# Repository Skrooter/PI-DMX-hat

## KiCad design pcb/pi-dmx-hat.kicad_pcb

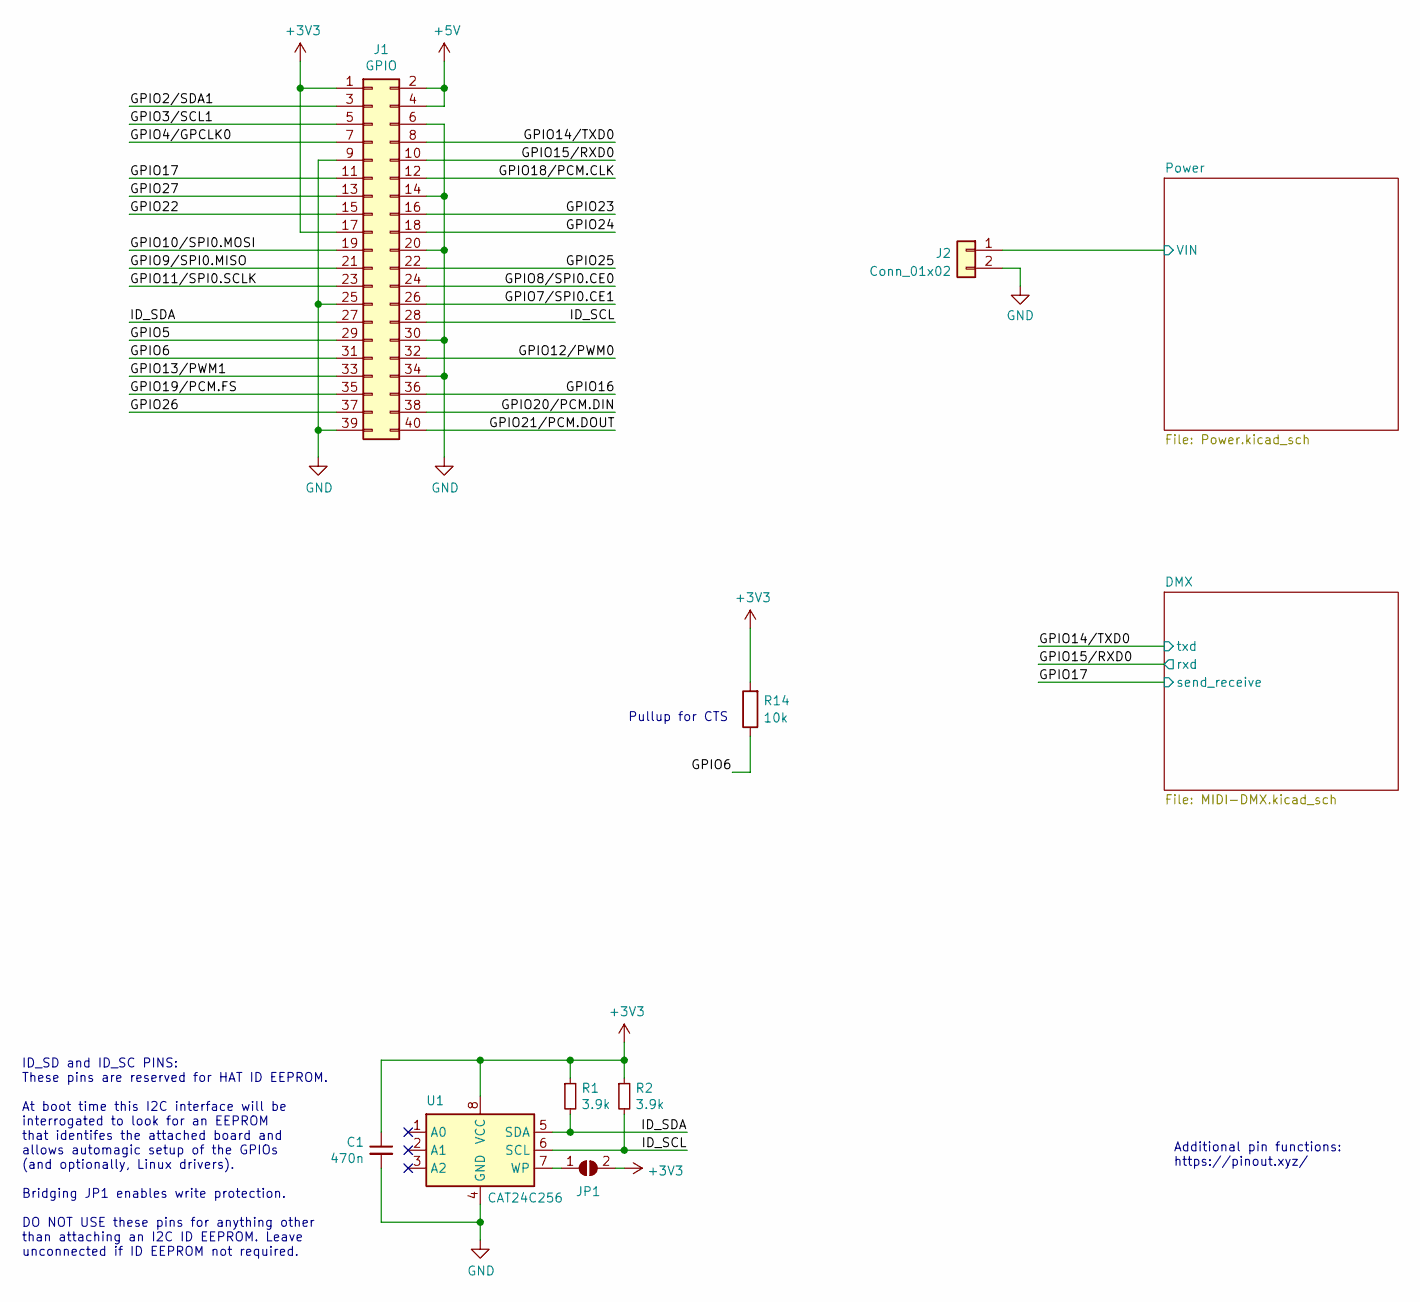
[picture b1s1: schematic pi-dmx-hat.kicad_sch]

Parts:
C1: 470n; C_0402_1005Metric; LCSC C307331
J1: GPIO; PinSocket_2x20_P2.54mm_Vertical
J2: Conn_01x02; PhoenixContact_MC_1,5_2-G-3.81_1x02_P3.81mm_Horizontal
JP1: ID_WP; SolderJumper-2_P1.3mm_Open_TrianglePad1.0x1.5mm
R1, R2: 3.9k; R_0603_1608Metric; LCSC C23018
R14: 10k; R_0402_1005Metric; LCSC C25744
U1: CAT24C256; DFN-8-1EP_3x2mm_P0.5mm_EP1.3x1.5mm; LCSC C233771

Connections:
+3V3: C1.1, J1.1, J1.17, JP1.2 (B), R1.1, R2.1, R14.2, U1.8 (VCC); also elsewhere on the board
+5V: J1.2, J1.4; also elsewhere on the board
/GPIO2/SDA1: J1.3
/GPIO3/SCL1: J1.5
/GPIO4/GPCLK0: J1.7
/GPIO5: J1.29
/GPIO6: J1.31, R14.1
/GPIO7/SPI0.CE1: J1.26
/GPIO8/SPI0.CE0: J1.24
/GPIO9/SPI0.MISO: J1.21
/GPIO10/SPI0.MOSI: J1.19
/GPIO11/SPI0.SCLK: J1.23
/GPIO12/PWM0: J1.32
/GPIO13/PWM1: J1.33
/GPIO14/TXD0: J1.8; also elsewhere on the board
/GPIO15/RXD0: J1.10; also elsewhere on the board
/GPIO16: J1.36
/GPIO17: J1.11; also elsewhere on the board
/GPIO18/PCM.CLK: J1.12
/GPIO19/PCM.FS: J1.35
/GPIO20/PCM.DIN: J1.38
/GPIO21/PCM.DOUT: J1.40
/GPIO22: J1.15
/GPIO23: J1.16
/GPIO24: J1.18
/GPIO25: J1.22
/GPIO26: J1.37
/GPIO27: J1.13
/ID_SCL: J1.28, R2.2, U1.6 (SCL)
/ID_SDA: J1.27, R1.2, U1.5 (SDA)
/Power/VIN: J2.1; also elsewhere on the board
GND: C1.2, J1.6, J1.9, J1.14, J1.20, J1.25, J1.30, J1.34, J1.39, J2.2, U1.4 (GND); also elsewhere on the board
unnamed: JP1.1 (A), U1.7 (WP)

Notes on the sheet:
Additional pin functions: https://pinout.xyz/
ID_SD and ID_SC PINS: These pins are reserved for HAT ID EEPROM. At boot time this I2C interface will be interrogated to look for an EEPROM that identifes the attached board and allows automagic setup of the GPIOs (and optionally, Linux drivers). Bridging JP1 enables write protection. DO NOT USE th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
Pullup for CTS

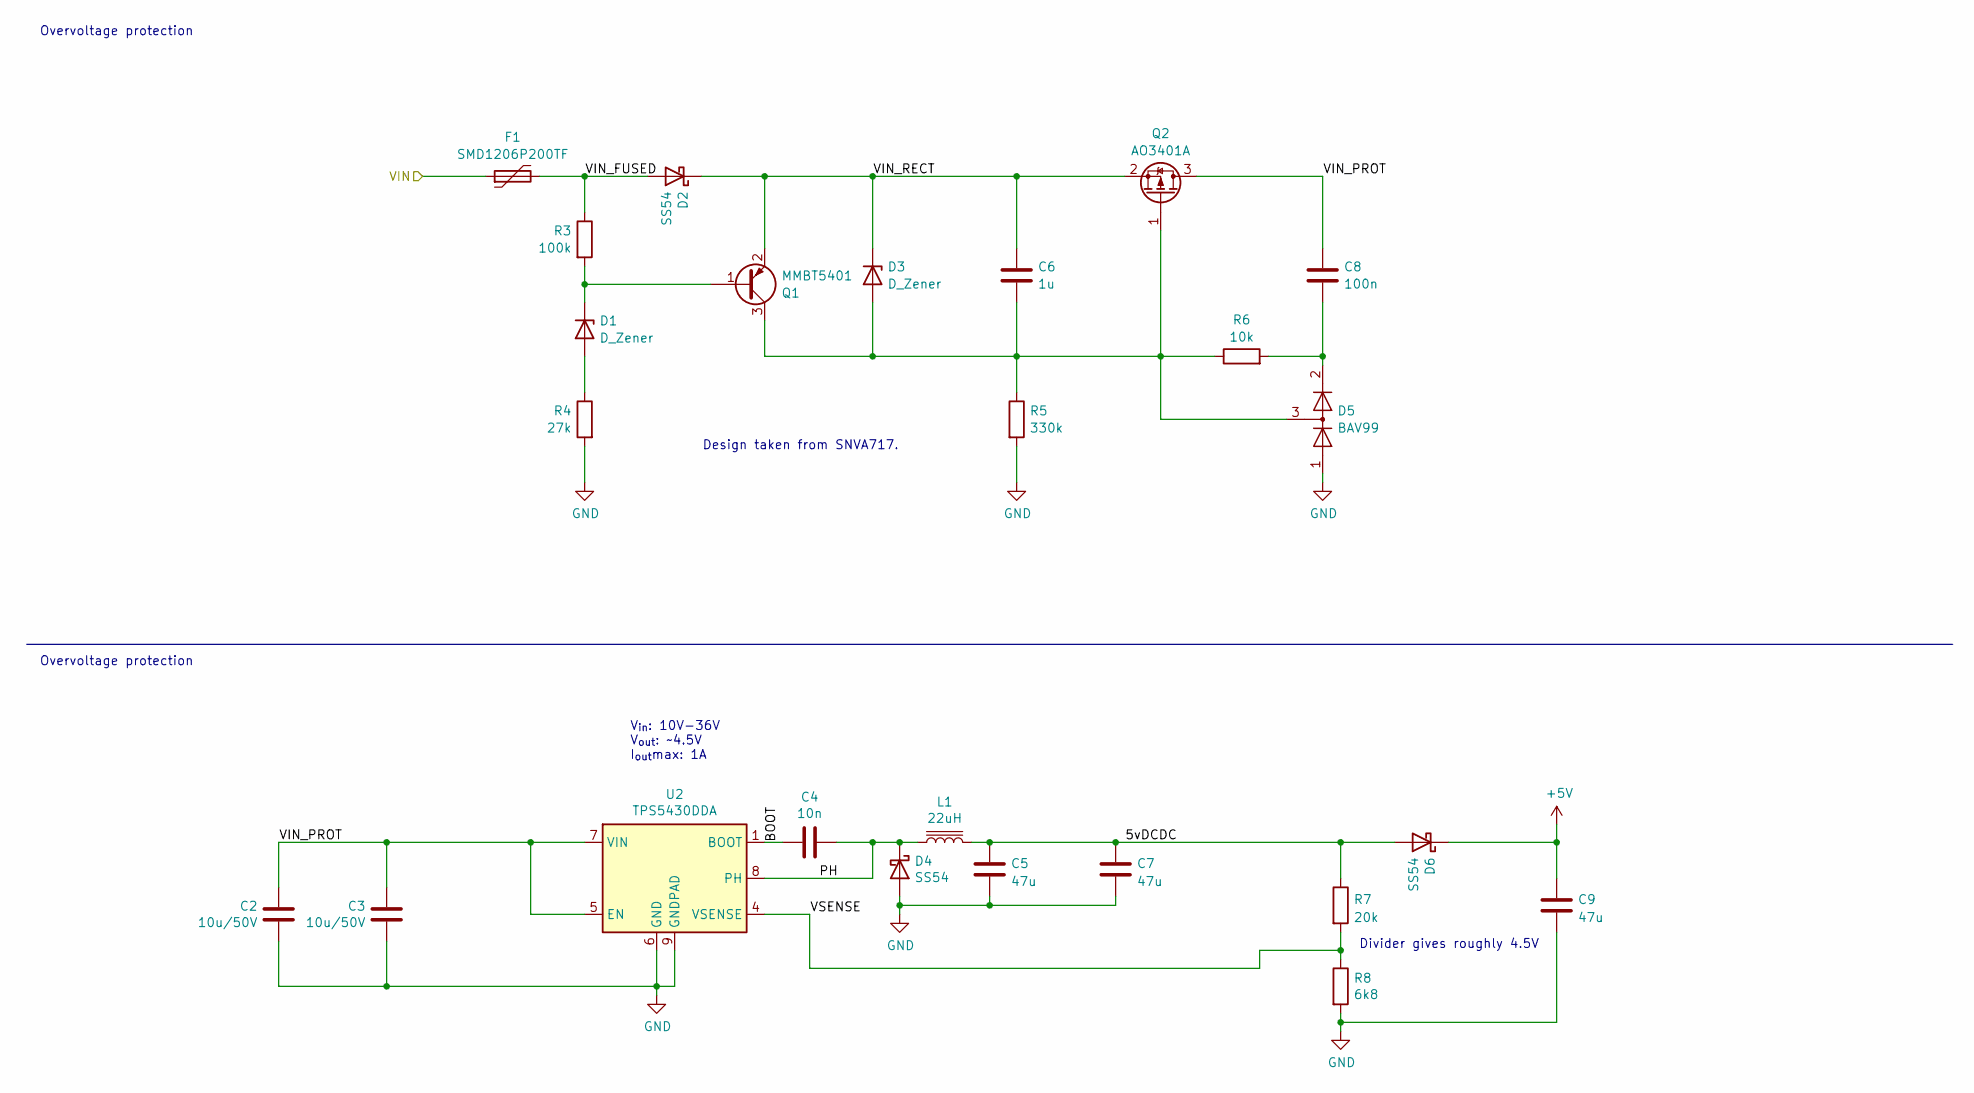
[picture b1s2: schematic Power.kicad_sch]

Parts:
C2, C3: 10u/50V; C_1206_3216Metric_Pad1.33x1.80mm_HandSolder; LCSC C13585
C4: 10n; C_0603_1608Metric_Pad1.08x0.95mm_HandSolder; LCSC C57112
C5, C7, C9: 47u; C_0805_2012Metric; LCSC C1779
C6: 1u; C_0805_2012Metric; LCSC C28323
C8: 100n; C_0402_1005Metric; LCSC C307331
D1, D3: D_Zener; D_SOD-123; LCSC C209348
D2, D4, D6: SS54; D_SMA; LCSC C22452
D5: BAV99; SOT-23; LCSC C2500
F1: SMD1206P200TF; Fuse_1206_3216Metric; LCSC C20988
L1: 22uH; L_Vishay_IHLP-4040; LCSC C845072
Q1: MMBT5401; SOT-23; LCSC C8326
Q2: AO3401A; SOT-23; LCSC C15127
R3: 100k; R_0402_1005Metric; LCSC C25741
R4: 27k; R_0603_1608Metric; LCSC C22967
R5: 330k; R_0603_1608Metric; LCSC C23137
R6: 10k; R_0402_1005Metric; LCSC C25744
R7: 20k; R_0603_1608Metric_Pad0.98x0.95mm_HandSolder; LCSC C4184
R8: 6k8; R_0603_1608Metric_Pad0.98x0.95mm_HandSolder; LCSC C23212
U2: TPS5430DDA; TI_SO-PowerPAD-8_ThermalVias; LCSC C9864

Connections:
+5V: C9.1, D6.1 (K); also elsewhere on the board
/Power/5vDCDC: C5.1, C7.1, D6.2 (A), L1.2, R7.1
/Power/BOOT: C4.2, U2.1 (BOOT)
/Power/PH: C4.1, D4.1 (K), L1.1, U2.8 (PH)
/Power/VIN: F1.1; also elsewhere on the board
/Power/VIN_FUSED: D2.2 (A), F1.2, R3.1
/Power/VIN_PROT: C2.2, C3.2, C8.1, Q2.3 (D), U2.5 (EN), U2.7 (VIN)
/Power/VIN_RECT: C6.1, D2.1 (K), D3.1 (K), Q1.2 (E), Q2.2 (S)
/Power/VSENSE: R7.2, R8.1, U2.4 (VSENSE)
GND: C2.1, C3.1, C5.2, C7.2, C9.2, D4.2 (A), D5.1 (K), R4.2, R5.2, R8.2, U2.6 (GND), U2.9 (GNDPAD); also elsewhere on the board
unnamed: D1.2 (A), R4.1
unnamed: D1.1 (K), Q1.1 (B), R3.2
unnamed: C6.2, D3.2 (A), D5.3 (K), Q1.3 (C), Q2.1 (G), R5.1, R6.1
unnamed: C8.2, D5.2 (A), R6.2

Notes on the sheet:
Divider gives roughly 4.5V
Overvoltage protection
V_{in}: 10V-36V V_{out}: ~4.5V I_{out}max: 1A
Design taken from SNVA717.

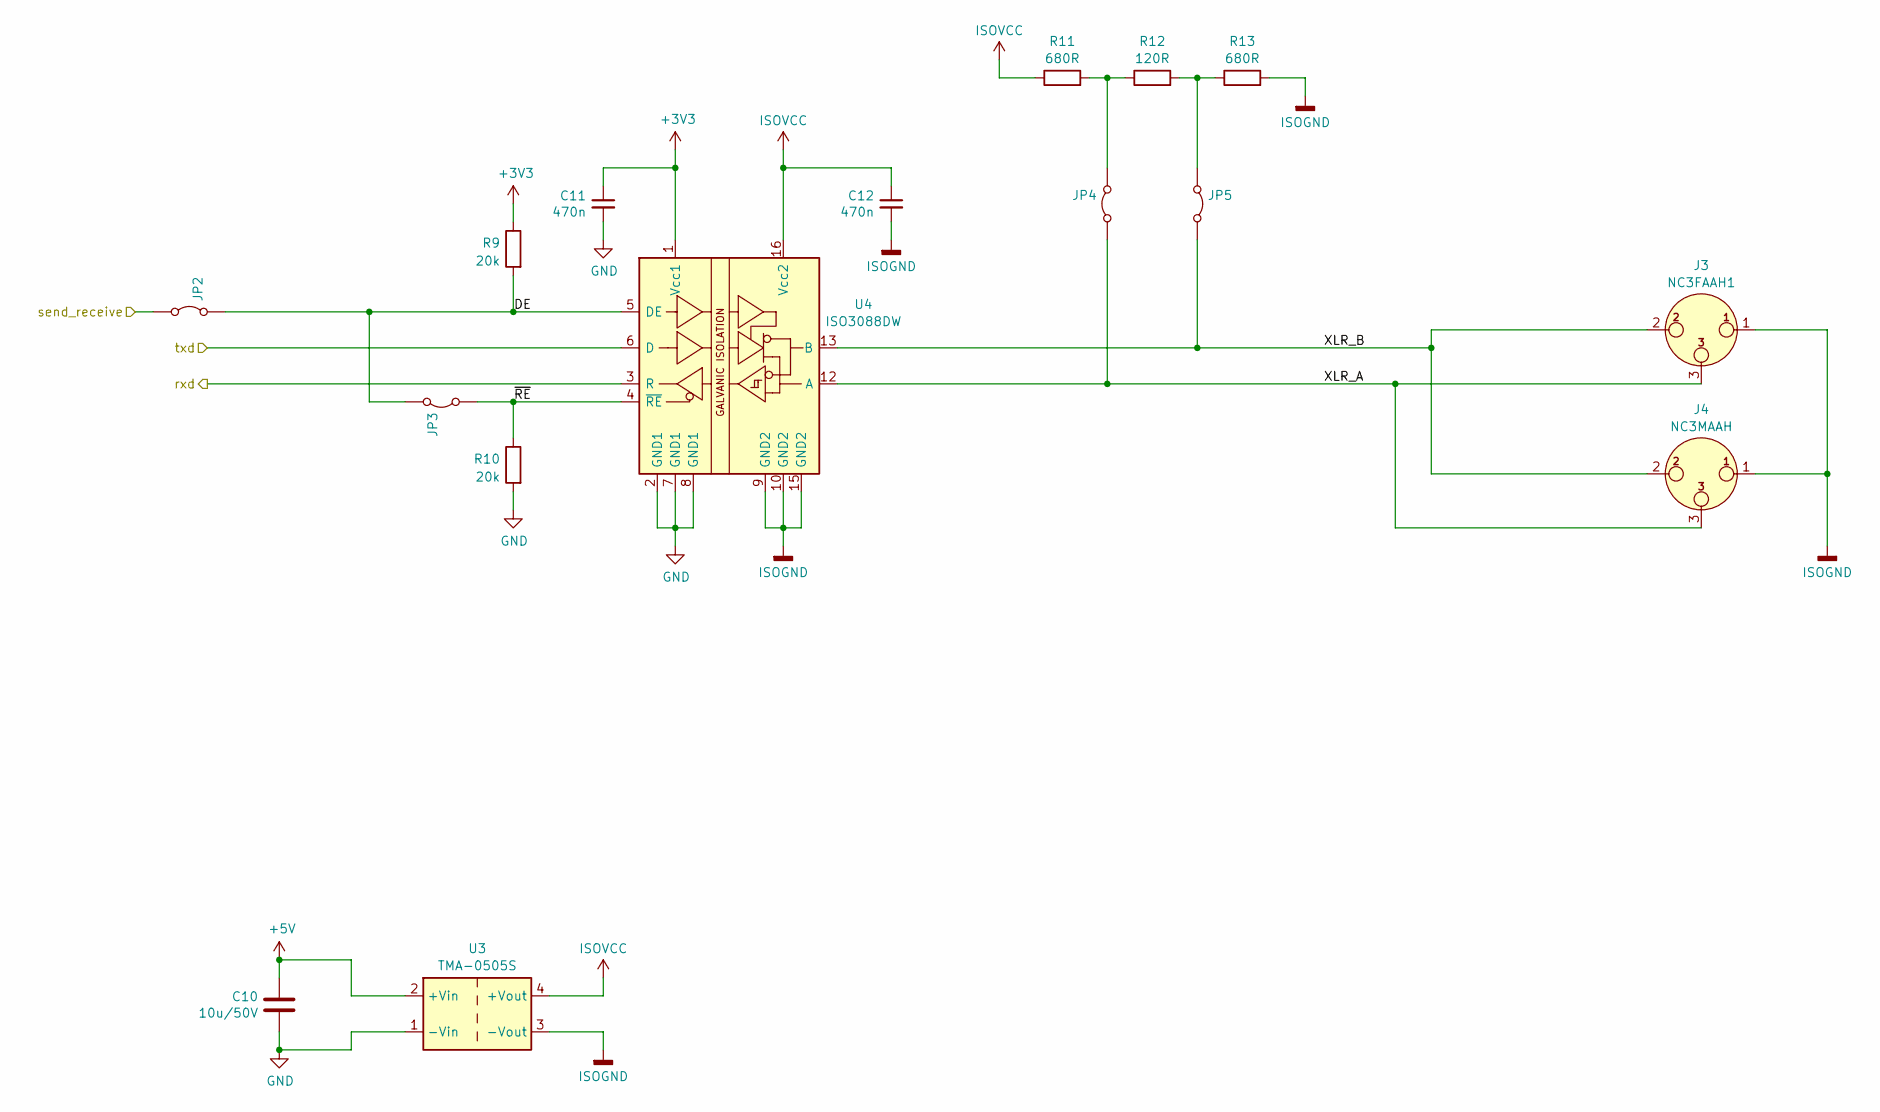
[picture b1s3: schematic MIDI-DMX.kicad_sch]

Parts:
C10: 10u/50V; C_1206_3216Metric_Pad1.33x1.80mm_HandSolder; LCSC C13585
C11, C12: 470n; C_0402_1005Metric; LCSC C307331
J3: NC3FAAH1; Jack_XLR_Neutrik_NC3FAAH1_Horizontal
J4: NC3MAAH; Jack_XLR_Neutrik_NC3MAAH-1_Horizontal
JP2, JP3, JP4, JP5: Jumper_2_Bridged; SolderJumper-2_P1.3mm_Bridged2Bar_Pad1.0x1.5mm
R9, R10: 20k; R_0603_1608Metric_Pad0.98x0.95mm_HandSolder; LCSC C4184
R11, R13: 680R; R_0805_2012Metric; LCSC C17772
R12: 120R; R_1206_3216Metric; LCSC C17909
U3: TMA-0505S; Converter_DCDC_Murata_MEE1SxxxxSC_THT; LCSC C7465127
U4: ISO3088DW; SOIC-16W_7.5x10.3mm_P1.27mm; LCSC C970943

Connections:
+3V3: C11.1, R9.1, U4.1 (Vcc1); also elsewhere on the board
+5V: C10.2, U3.2 (+Vin); also elsewhere on the board
/DMX/DE: JP2.1 (A), JP3.1 (A), R9.2, U4.5 (DE)
/DMX/XLR_A: J3.3, J4.3, JP4.2 (B), U4.12 (A)
/DMX/XLR_B: J3.2, J4.2, JP5.2 (B), U4.13 (B)
/DMX/~RE: JP3.2 (B), R10.1, U4.4 (~RE)
/GPIO14/TXD0: U4.6 (D); also elsewhere on the board
/GPIO15/RXD0: U4.3 (R); also elsewhere on the board
/GPIO17: JP2.2 (B); also elsewhere on the board
GND: C10.1, C11.2, R10.2, U3.1 (-Vin), U4.2 (GND1), U4.7 (GND1), U4.8 (GND1); also elsewhere on the board
ISOGND: C12.2, J3.1, J4.1, R13.2, U3.3 (-Vout), U4.9 (GND2), U4.10 (GND2), U4.15 (GND2)
ISOVCC: C12.1, R11.1, U3.4 (+Vout), U4.16 (Vcc2)
unnamed: JP4.1 (A), R11.2, R12.1
unnamed: JP5.1 (A), R12.2, R13.1

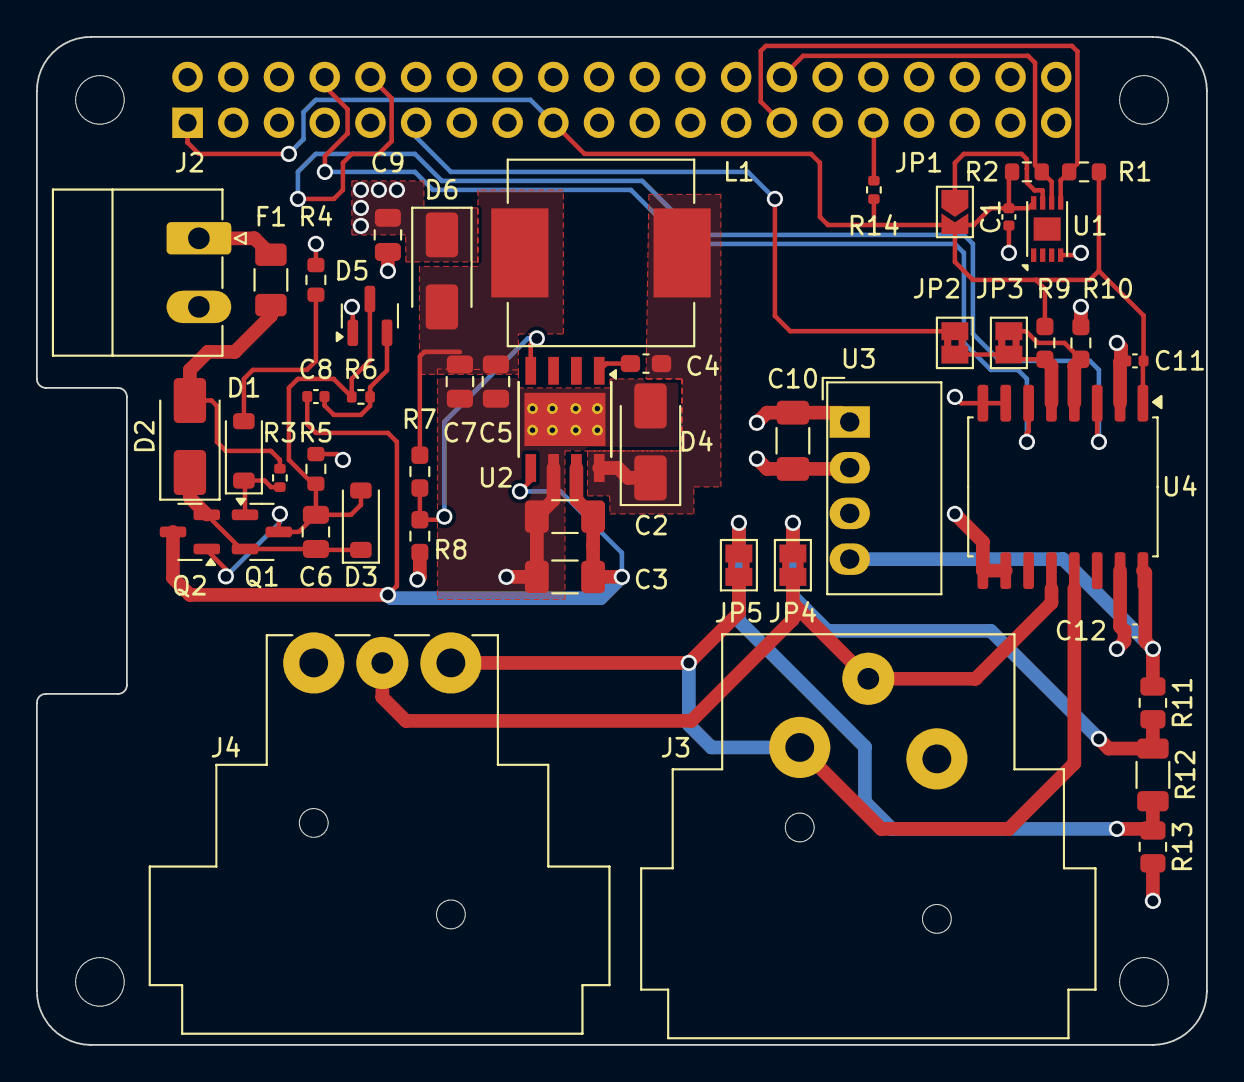
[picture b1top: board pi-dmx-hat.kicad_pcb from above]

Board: 4 copper layers, 65.0 x 56.0 mm, 53 parts (1 on the bottom side), 30 nets.

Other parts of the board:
MH1, MH2, MH3, MH4: MountingHole_2.7mm_M2.5

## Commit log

2024-08-07 Inital schematic ready for production
